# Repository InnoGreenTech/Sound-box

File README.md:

# Sound-box
Sound box player with Arduino nano and DFPLAYER. Random play with push button and DLR résistor

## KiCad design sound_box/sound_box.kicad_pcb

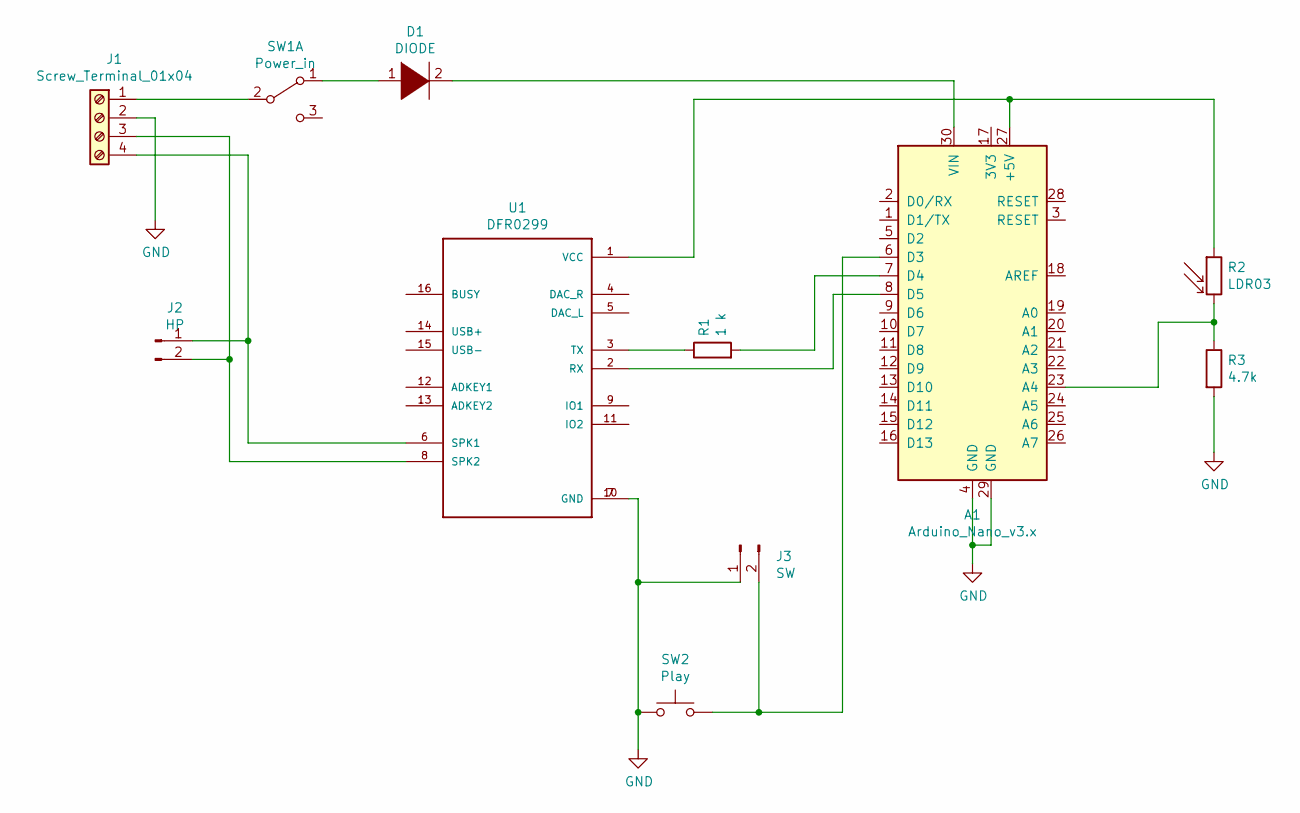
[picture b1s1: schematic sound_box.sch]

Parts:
A1: Arduino_Nano_v3.x; Arduino_Nano
D1: DIODE; D_DO-34_SOD68_P7.62mm_Horizontal
J1: Screw_Terminal_01x04; TerminalBlock_MetzConnect_Type086_RT03404HBLC_1x04_P3.81mm_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
J2: HP; SolderWirePad_1x02_P3.81mm_Drill1mm
J3: SW; SolderWirePad_1x02_P3.81mm_Drill1mm
R1: 1 k; R_Axial_DIN0207_L6.3mm_D2.5mm_P10.16mm_Horizontal
R2: LDR03; R_LDR_5.0x4.1mm_P3mm_Vertical
R3: 4.7k; R_Axial_DIN0207_L6.3mm_D2.5mm_P10.16mm_Horizontal
SW1: Power_in; SW_CuK_OS102011MA1QN1_SPDT_Angled
SW2: Play; SW_PUSH_6mm_H5mm
U1: DFR0299; MODULE_DFR0299

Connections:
GND: A1.4 (GND), A1.29 (GND), J1.2, J3.1, R3.2, SW2.1, U1.7 (GND), U1.10 (GND)
unnamed: A1.6 (D3), J3.2, SW2.2
unnamed: A1.7 (D4), R1.2
unnamed: A1.8 (D5), U1.2 (RX)
unnamed: A1.23 (A4), R2.2, R3.1
unnamed: A1.27 (+5V), R2.1, U1.1 (VCC)
unnamed: A1.30 (VIN), D1.2 (A)
unnamed: D1.1 (K), SW1.1 (A)
unnamed: J1.1, SW1.2 (B)
unnamed: J1.3, J2.2, U1.8 (SPK2)
unnamed: J1.4, J2.1, U1.6 (SPK1)
unnamed: R1.1, U1.3 (TX)

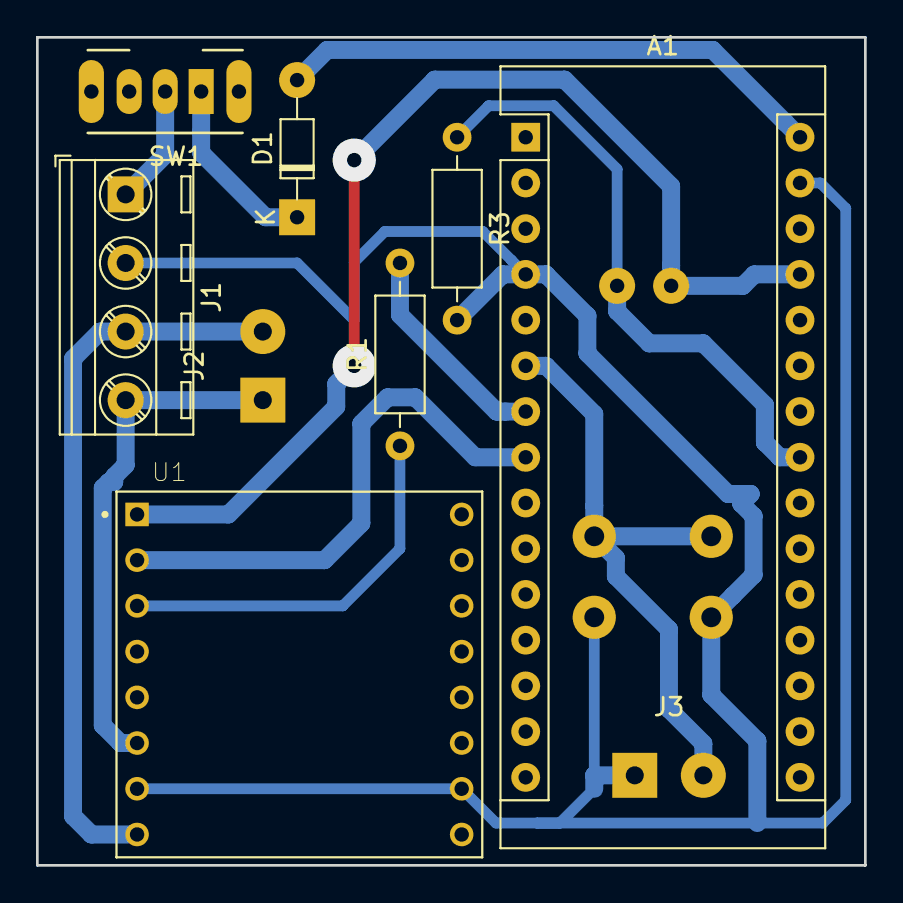
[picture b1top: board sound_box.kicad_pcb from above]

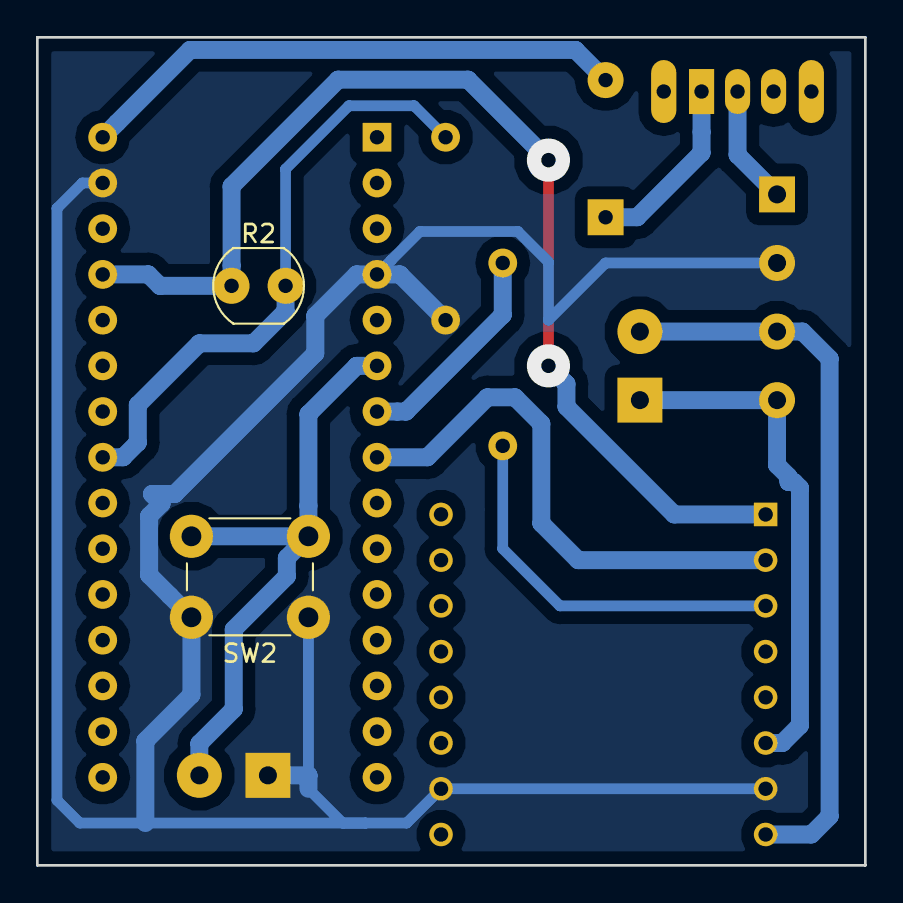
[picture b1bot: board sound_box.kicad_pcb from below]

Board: 2 copper layers, 46.0 x 46.0 mm, 11 parts (2 on the bottom side), 12 nets.

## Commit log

2020-07-02 add project initial version
2021-02-06 add arduino code
